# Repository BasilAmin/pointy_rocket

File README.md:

# 🚀 Pointy Rocket V1

**Pointy Rocket** is an actively stabilised model-scale rocket developed by the Engineering Society of Castleknock College (SVCC). It uses **Thrust Vector Control (TVC)** — the same technique used in orbital-class rockets — to actively stabilise the vehicle in flight.

The project spans custom PCB hardware design, embedded flight firmware, and a high-fidelity physics simulation, all living in this repository.

---

> **An SVCC Project with support from RS Components**
> &nbsp;&nbsp;&nbsp;&nbsp;&nbsp;&nbsp;&nbsp;&nbsp;&nbsp;&nbsp;&nbsp;&nbsp;

---

## Authors

- James Harcourt
- Basil Amin
- Ashkan Samali
- Feargal Browne
- Ben Liu
- Ryan Doran

---

## Project Overview

| Component     | Details                                                             |
|---------------|---------------------------------------------------------------------|
| Stabilisation | 2-axis Thrust Vector Control (TVC) via servo-gimballed motor mount  |
| Motors        | 4× Estes D12 (clustered)                                            |
| Microcontroller | Teensy 4.1 (NXP i.MX RT1062, Cortex-M7 @ 600 MHz)               |
| IMU           | MPU6050 (6-axis accelerometer + gyroscope, I2C)                     |
| Altimeter     | MPL3115A2 barometric altimeter                                      |
| Data Logging  | SD card (SPI)                                                       |
| Recovery      | Parachute deployment                                                |

---

## Repository Structure

```
pointy_rocket/
├── Dictator_Flight_Firmware/   # Main embedded flight firmware (Teensy 4.1 / PlatformIO)
├── Firmware_test/              # Firmware testing scripts and utilities
├── hardware/                   # KiCad PCB schematic & layout
│   └── pcb/
│       └── Pointy R1 Flight controller/
│           ├── *.kicad_sch
│           ├── *.kicad_pcb
│           ├── symbols.kicad_sym
│           └── footprints.pretty/
├── simulation/                 # Python flight simulation suite
│   ├── rocket_sim.py           # Full 6-DOF 3D simulation (RK4 + Quaternions)
│   ├── tvc_sim.py              # TVC-controlled flight engine
│   ├── rocketpy_engine.py      # RocketPy aerodynamics integration
│   ├── rocketpy_adapter.py     # Hybrid engine orchestrator
│   ├── motor_curve.py          # Thrust curve parser (.eng / .rse / .csv)
│   ├── motor_sweep.py          # Motor configuration parameter sweep
│   ├── gui_server.py           # Browser-based TVC simulator GUI
│   ├── plots.py                # Standalone matplotlib figure generator
│   ├── pygame_simulation.py    # Pygame visualisation
│   ├── requirements.txt
│   └── simulation_results.png
├── Media/                      # Logos and media assets
├── Pointy R1 Flight controller.csv  # BOM / component list
├── sim_specs.txt               # Simulation variable reference
└── .gitignore
```

---

## Firmware

The flight computer runs on a **Teensy 4.1**, programmed via PlatformIO with the Arduino framework. The firmware reads IMU data, runs a PID controller, and drives the two TVC servos in real time.

### Hardware

| Component       | Details                                          |
|-----------------|--------------------------------------------------|
| Microcontroller | Teensy 4.1 (NXP i.MX RT1062, Cortex-M7 @ 600 MHz) |
| IMU             | MPU6050 (6-axis accelerometer + gyroscope, I2C)  |
| Altimeter       | MPL3115A2 barometric altimeter                   |
| Actuation       | 2× Servo (dual-axis TVC gimbal)                  |
| Data Logging    | SD card (SPI)                                    |
| Power           | AMASS XT60 connector                             |
| Ignition        | N-MOSFET (D2PAK) motor ignition circuit          |

### Dependencies

| Library                   | Version  |
|---------------------------|----------|
| `arduino-libraries/Servo` | `^1.3.0` |
| `electroniccats/MPU6050`  | `^1.4.4` |
| `arduino-libraries/SD`    | `^1.3.0` |

### Build & Flash

**Prerequisites:** [PlatformIO](https://platformio.org/) (CLI or VS Code extension)

```bash
# Clone the repo
git clone https://github.com/BasilAmin/pointy_rocket.git
cd pointy_rocket/Dictator_Flight_Firmware

# Build
pio run

# Flash to Teensy (press the button on the board if needed)
pio run --target upload

# Open serial monitor
pio device monitor
```

---

## Hardware / PCB

The custom flight controller PCB is designed in **KiCad** and lives in `hardware/pcb/Pointy R1 Flight controller/`. Custom symbols and footprints are included for:

- Teensy 4.1 (form-factor reference)
- MPU6050 breakout (GY-521 module)
- MPL3115A2 barometric altimeter
- AMASS XT60 power connector
- N-MOSFET (D2PAK) motor ignition circuit
- Tactile and slide switches
- Passive components (diode, SOT-23 transistor)

To open the design, install [KiCad 7+](https://www.kicad.org/) and open `Pointy R1 Flight controller.kicad_pro`.

---

## Simulation

The simulation suite models the full flight from ignition through parachute landing. It uses a hybrid approach combining the trusted aerodynamics of **RocketPy** with a custom in-house **TVC 6-DOF engine**.

### Architecture

Because Pointy Rocket is a finless TVC rocket (unstable by design), a purely passive simulation cannot fly it. The two engines are combined to play to each other's strengths:

- **RocketPy** (`rocketpy_engine.py`) provides trusted aerodynamics: Barrowman centre of pressure, static margin, a real atmosphere model. It cannot model thrust vectoring, so it cannot fly the rocket passively.
- **The in-house TVC sim** (`tvc_sim.py`) flies the actively steered rocket (quaternion 6-DOF, RK4, PID gimbal), using RocketPy's centre of pressure and drag values instead of a rough analytic estimate.

`rocketpy_adapter.py` orchestrates both and returns side-by-side results.

### Setup

```bash
cd simulation
python -m venv .venv && source .venv/bin/activate   # Windows: .venv\Scripts\activate
pip install -r requirements.txt
```

Requirements: `numpy`, `matplotlib`, `rocketpy` (which pulls in `scipy` and `netCDF4`).

### TVC Simulator GUI

A browser-based GUI wraps both flight engines and lets you upload or fetch motor files, import body geometry, and view results interactively.

```bash
cd simulation
python gui_server.py
```

Open `http://127.0.0.1:8765`. Each run renders a **matplotlib** figure (altitude, thrust curve, TVC gimbal angles, speed/mass) shown below the live chart with a PNG download link.

The same figure can be produced from the command line:

```bash
python plots.py path/to/motor.eng    # writes matplotlib_results.png
```

### Flight computer in the loop

The TVC sim does not steer with perfect knowledge — it runs a realistic flight-computer model (`flight_computer.py`) matched to the actual hardware (MPU6050 read at its ±2 g / ±250 °/s defaults; two servos on the Arduino `Servo` library = 1° write resolution):

- **MPU6050 sensor model** — per-flight gyro/accel bias, white noise, range clipping and 16-bit quantisation.
- **Attitude estimator** — gyro integration with on-pad calibration. (In flight a rocket's accelerometer can't sense gravity — under thrust it reads thrust, in coast it's in free fall — so the accelerometer is used only on the pad to set the initial attitude and the gyro bias. This is the reference algorithm for the Teensy firmware.)
- **Discrete PID** at the configured control rate with control-loop **latency**.
- **Servo model** — slew-rate limit, command resolution, deadband and lag.

Two findings this exposes: residual **gyro-bias drift** is the dominant attitude error, and because thrust vectoring needs thrust, the rocket is only controllable **during the burn** — after burnout a finless vehicle tumbles (expected; recovery is by parachute). Stability is therefore judged over the powered phase.

### Monte-Carlo dispersion

`montecarlo.py` runs many flights with the uncertain parameters perturbed (mass, propellant, motor thrust, drag, centre of pressure, wind, thrust misalignment, sensor bias/noise) and reports the distribution of apogee, powered-phase tilt, gimbal usage and landing radius, plus the fraction of flights that stay controlled during burn. RocketPy aerodynamics are evaluated once for the nominal vehicle; flights run in parallel across CPU cores.

```bash
python montecarlo.py path/to/motor.eng 200 path/to/rocket.ork
```

### 6-DOF Flight Simulation

`rocket_sim.py` implements a full **6 Degrees of Freedom** rigid-body simulation:

- **RK4 numerical integration** for accurate state propagation
- **Quaternion-based attitude representation** (no gimbal lock)
- **PID controller** for dual-axis TVC stabilisation
- **Dynamic mass model** — propellant mass decreases with cumulative impulse
- **High-fidelity D12 thrust curve** (4× scaled cluster, from verified RASP data)
- **Aerodynamic drag** with wind shear model
- **Automatic parachute deployment** on descent

#### PID Controller Parameters

| Gain             | Value |
|------------------|-------|
| Kp               | 0.8   |
| Kd               | 1.5   |
| Ki               | 0     |
| Max gimbal angle | ±8°   |

```bash
python rocket_sim.py
```

Outputs a 4-panel plot (`simulation_results.png`) showing:

- 3D flight trajectory
- Altitude vs. time
- Dual-axis TVC gimbal angles
- Dynamic mass and thrust profile

### Motor Configuration Sweep

`motor_sweep.py` sweeps across 1–4 motor configurations to compare predicted performance across different cluster sizes.

```bash
python motor_sweep.py
```

---

## Language Breakdown

| Language   | Share  |
|------------|--------|
| C++        | 81.2%  |
| Python     | 9.7%   |
| C          | 6.0%   |
| JavaScript | 1.2%   |
| Processing | 0.9%   |
| HTML       | 0.6%   |
| Other      | 0.4%   |

---

## License

MIT License — © 2026 Basil Amin. See [LICENSE](firmware/LICENSE) for details.
## License

MIT License — © 2026 Basil Amin. See [LICENSE](firmware/LICENSE) for details.

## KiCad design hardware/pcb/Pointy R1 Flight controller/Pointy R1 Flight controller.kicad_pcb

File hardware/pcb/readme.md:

# Pointy R1 Flight Controller PCB

Custom flight controller board designed in KiCad for the Pointy R1 rocket. Handles motor control, sensor fusion, audio/visual feedback, and power regulation.

## Directory Structure

```
Pointy R1 Flight controller/
├── Pointy R1 Flight controller.kicad_pro   # KiCad project file
├── Pointy R1 Flight controller.kicad_sch   # Schematic
├── Pointy R1 Flight controller.kicad_pcb   # PCB layout
├── Pointy R1 Flight controller.csv         # Bill of materials
├── 3d Models/                              # STEP files for 3D viewer
└── Pointy R1 Flight controller-backups/    # KiCad auto-backups
```

## Bill of Materials

| Ref | Qty | Part | Description |
|-----|-----|------|-------------|
| IC1 | 1 | Teensy 4.1 | Main microcontroller |
| U2 | 1 | GY-521 (MPU-6050) | 6-axis IMU (accel + gyro) |
| U3 | 1 | MPL3115A2 | Barometric pressure / altitude sensor |
| U1 | 1 | L7805CV | 5V linear voltage regulator (TO-220) |
| Q1, Q2, Q3 | 3 | IRLZ44NSTRLPBF | N-channel MOSFET for motor/actuator control |
| D1 | 1 | 1N5822 | Schottky diode (flyback protection) |
| D2, D3, D4 | 3 | 1N4007 | Rectifier diodes |
| M1, M2 | 2 | Servo header | 3-pin 2.54 mm servo connectors |
| P1–P4 | 4 | 282837-2 | 2-pos screw terminals (TE Connectivity) |
| J3 | 1 | XT60-M | Main battery connector |
| LED1 | 1 | COM-16347 | RGB LED (SparkFun) |
| LS1 | 1 | CMI-1295-0585T | Piezo buzzer |
| S2 | 1 | TS02-66-70-BK-100-LCR-D | Tactile push button |
| C1 | 1 | 10 µF | Bulk decoupling (0805) |
| C2 | 1 | 1 µF | Mid-frequency decoupling (0805) |
| C3 | 1 | 100 nF | High-frequency decoupling (0805) |
| R2, R3, R5, R7 | 4 | 470 Ω | Current-limiting resistors (0805) |
| R8 | 1 | 10 kΩ | Pull-up/pull-down resistor (0805) |
| R9 | 1 | 4.7 kΩ | Pull-up/pull-down resistor (0805) |

## Design Notes

- **Power input:** XT60 connector → L7805CV regulates down to 5 V for logic. Teensy 4.1 runs at 3.3 V internally.
- **Motor/actuator outputs:** Three IRLZ44N logic-level MOSFETs switch inductive loads; flyback diodes (1N4007) on each gate, 1N5822 on the rail.
- **IMU:** GY-521 module (MPU-6050) connected via I2C for attitude estimation.
- **Altimeter:** MPL3115A2 on I2C for altitude and vertical speed.
- **Feedback:** RGB LED and piezo buzzer for status/alarm indication.
- **Programming:** Teensy 4.1 programs over USB; no additional programmer needed.
- **PCB has passed DFM review** — Gerbers ready for manufacture (see git history).

## Opening the Project

Requires **KiCad 7+**. Open `Pointy R1 Flight controller/Pointy R1 Flight controller.kicad_pro`.

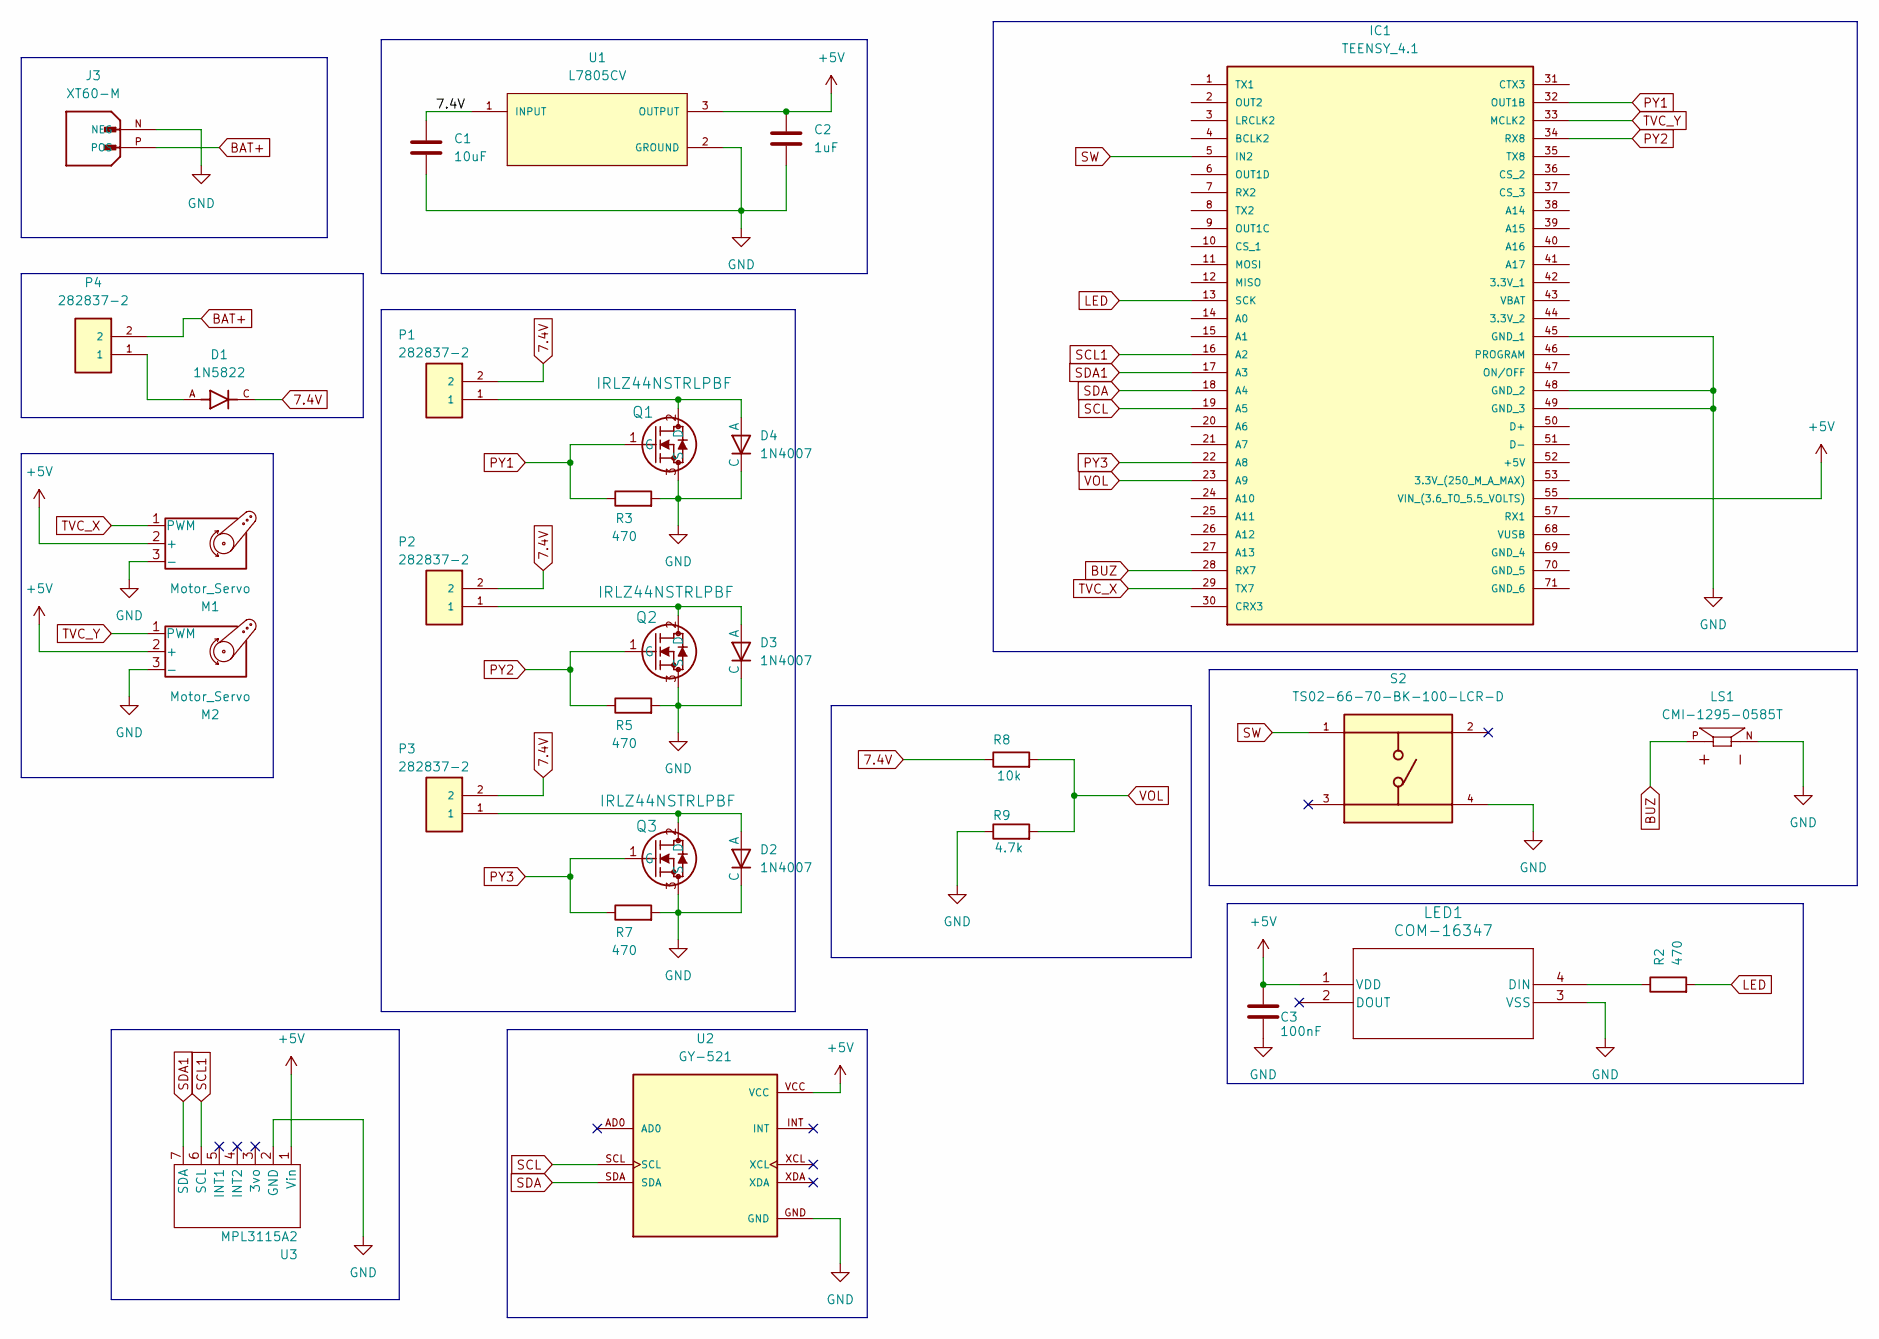
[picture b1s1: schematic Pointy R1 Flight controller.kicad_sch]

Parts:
C1: 10uF; C_0805_2012Metric
C2: 1uF; C_0805_2012Metric
C3: 100nF; C_0805_2012Metric
D1: 1N5822; DIOAD1990W125L900D530; PARTREV K2105
D2, D3, D4: 1N4007; P1_DO-41
IC1: TEENSY_4.1; TEENSY41; Manufacturer_Part_Number TEENSY 4.1
J3: XT60-M; AMASS_XT60-M; PARTREV V1.2
LED1: COM-16347; COM-16347_SPK
LS1: CMI-1295-0585T; CUI_CMI-1295-0585T; PARTREV N/A
M1, M2: Motor_Servo; PinHeader_1x03_P2.54mm_Vertical
P1, P2, P3, P4: 282837-2; TE_282837-2; PARTREV G3
Q1, Q2, Q3: IRLZ44NSTRLPBF; NMOSGDS_D2PAK_INF
R2, R3, R5, R7: 470; R_0805_2012Metric
R8: 10k; R_0805_2012Metric
R9: 4.7k; R_0805_2012Metric
S2: TS02-66-70-BK-100-LCR-D; SW_TS02-66-70-BK-100-LCR-D; PARTREV 1.0
U1: L7805CV; TO255P1040X460X1968-3; PARTREV 36
U2: GY-521; MODULE_GY-521; PARTREV NA
U3: MPL3115A2

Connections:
7.4V: C1.1, D1.C, P1.2, P2.2, P3.2, R8.1, U1.1 (INPUT)
+5V: C2.1, C3.1, IC1.55 (VIN_(3.6_TO_5.5_VOLTS)), LED1.1 (VDD), M1.2 (+), M2.2 (+), U1.3 (OUTPUT), U2.VCC, U3.1 (Vin)
BAT+: J3.P (POS), P4.2
BUZ: IC1.28 (RX7), LS1.P
GND: C1.2, C2.2, C3.2, D2.2 (C), D3.2 (C), D4.2 (C), IC1.45 (GND_1), IC1.48 (GND_2), IC1.49 (GND_3), J3.N (NEG), LED1.3 (VSS), LS1.N, M1.3 (-), M2.3 (-), Q1.3 (S), Q2.3 (S), Q3.3 (S), R3.2, R5.2, R7.2, R9.1, S2.4, U1.2 (GROUND), U2.GND, U3.2 (GND)
LED: IC1.13 (SCK), R2.2
unnamed: D1.A, P4.1
unnamed: D2.1 (A), P3.1, Q3.2 (D)
unnamed: D3.1 (A), P2.1, Q2.2 (D)
unnamed: D4.1 (A), P1.1, Q1.2 (D)
unnamed: LED1.4 (DIN), R2.1
PY1: IC1.32 (OUT1B), Q1.1 (G), R3.1
PY2: IC1.34 (RX8), Q2.1 (G), R5.1
PY3: IC1.22 (A8), Q3.1 (G), R7.1
SCL: IC1.19 (A5), U2.SCL
SCL1: IC1.16 (A2), U3.6 (SCL)
SDA: IC1.18 (A4), U2.SDA
SDA1: IC1.17 (A3), U3.7 (SDA)
SW: IC1.5 (IN2), S2.1
TVC_X: IC1.29 (TX7), M1.1 (PWM)
TVC_Y: IC1.33 (MCLK2), M2.1 (PWM)
VOL: IC1.23 (A9), R8.2, R9.2

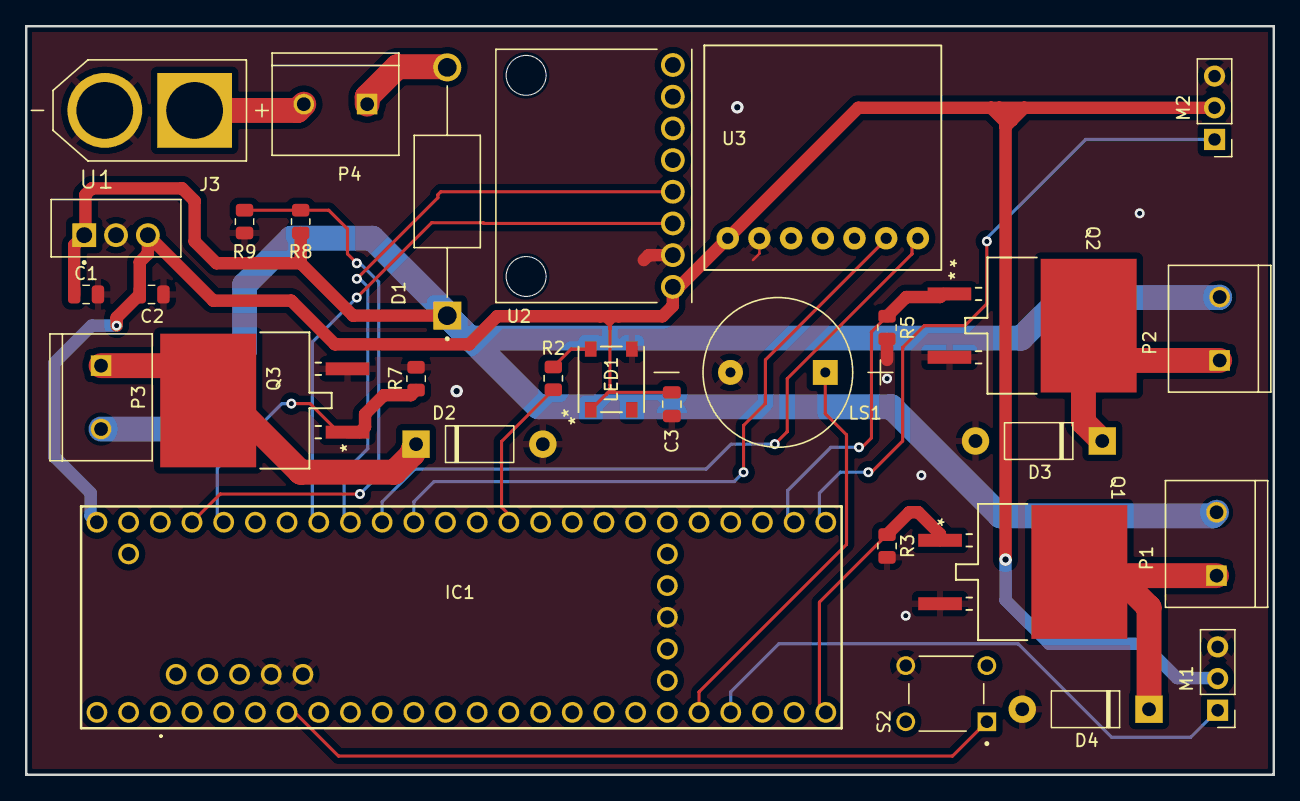
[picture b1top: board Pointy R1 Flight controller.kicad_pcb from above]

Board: 2 copper layers, 100.0 x 60.0 mm, 30 parts (0 on the bottom side), 22 nets.

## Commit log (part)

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2026-05-01 Update README to include TVC in title
2026-05-01 env setup
2026-05-01 Revise README with project details and introduction
    Updated project title and added introduction and components sections.
2026-05-02 Move all firmware files into the designated folder
2026-05-02 Move readme back to master folder
2026-05-02 pcb env set up
2026-05-02 create hardware and pcb development env
2026-05-03 create PCB library env, added main components to sch
2026-05-04 created symbol and schematic for MPL3115A2
2026-05-04 added majority of power connections + buses, wired MPL3115A2 altimeter and gy-521 imu
2026-05-04 added servos, pyro channels, voltage divider, switch, led, buzzer and xt60 connector. Made all connections
2026-05-05 Create sim_specs.txt with simulation variables
    Added fundamental simulation variables
2026-05-05 Connected voltage divider + removed floating Capacitors
2026-05-05 added schottky diode for reverse polarity protection, neatened +formated sch
2026-05-08 feat: add simulation folder
2026-05-08 feat: add fundamental rocket physics simulation script
2026-05-08 feat: update physics model with aerodynamics and Estes D12 cluster
2026-05-08 feat: upgrade to 2D Rigid Body Dynamics with active TVC
2026-05-08 feat: add video animation output using matplotlib FuncAnimation
2026-05-08 Update .gitignore and remove .DS_Store files to clean up repo
2026-05-08 Update simulation script and save results
2026-05-08 chore: tune TVC parameters for stability
2026-05-08 fix: invert TVC PID controller polarity and set vertical launch angle
2026-05-08 test: change launch angle to 88 degrees to test TVC disturbance rejection
2026-05-08 feat: add parachute recovery system and visualization
2026-05-08 Fix parachute rotational physics and add canopy animation
2026-05-08 Fix parachute oscillation bug with forced damping model
2026-05-08 Add motor parameter sweep script
2026-05-08 Implement RK4 integration and Kalman Filter (Phase 1 & 2)
2026-05-08 Implement RK4 physics, synthetic IMU, and Kalman Filter
    Core physics and control upgrades:
    - Replaced unstable Forward Euler integration with a 4th-Order Runge-Kutta
    (RK4) solver, preventing artificial energy drift during high-frequency
    oscillations.
    - Introduced continuous-time actuator modeling (servo lag) via a first-order
    differential equation, making TVC dynamics independent of frame rate.
2026-05-08 Implementing dynamic mass, shifting CG, and realistic thrust curves
    This replaces the static mass and simple step-function thrust with a fully dynamic model. The simulation now parses a realistic thrust curve and couples propellant mass loss directly to the accumulat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
2026-05-08 Implementing Phase 4: Wind shear and relative aerodynamics
    Added a horizontal wind profile that increases with altitude. The physics engine now calculates aerodynamic forces based on the rocket's velocity relative to the airmass rather than the ground frame,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
2026-05-08 Implementing full 6-DOF physics and quaternion-based rotation
2026-05-08 Error fix solving the 6-DOF Apogee Collapse
2026-05-09 IGNORE - add .ds_store to gitignore (housekeeping)
2026-05-09 Error fixes relating to starting at 100N, and being 132N instead of 120N
2026-05-09 Add requirements.txt for simulation dependencies
2026-05-09 Changed result file directory to a global (~) filew link, replacing drive name (D:)
2026-05-09 Added decoupling cap to WS2812b
2026-05-09 Replaced mosfets with higher current rated IRLZ44N
2026-05-09 Added 1N4007 flyback diodes for over voltage/current protection on mosfets
2026-05-09 Added 1N4007 flyback diodes to schematic + made neccisary connections
2026-05-10 Created .pcb document, pcb outline and placed all components on the board
2026-05-13 Add files via upload
    Live simulation for making the PID controller, currently no turbulence or PID controller. Also torque is probably calculated wrong
2026-05-13 Routed majority of traces for all components, excluding minor power management and gnd plane tasks
2026-05-13 Completed routing and added gnd plane, completeting v1 of the PFC - ready for drm
2026-05-14 Clean up .gitignore by removing conflict markers
    Removed merge conflict markers and cleaned up .gitignore.
2026-05-14 Fixed various issues on PCB, genrated gbr files - ready for dfm
2026-05-14 Generated Gerber zip file
2026-05-16 Ran DFM + updated pcb accordingly. New gbr files generated
2026-06-05 Added 3d Models to PCB for teensy + Mosfets
2026-06-10 create PCB readme
2026-06-10 Add RS logo to project files
2026-06-10 Rename RS Logo file
2026-06-10 Add SVCC logo to media files
